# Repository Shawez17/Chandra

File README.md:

High Voltage Power Supply+ (remote operation)
=========================

```Markdown
1. When encoder rotates or value form the pc (out of 4086) is entered
# provides V out values on the display
# provide I out values on the display aswell, same goes for V in
2. When machine[esp32 and mains both] turned on.
# Led indicator glows
# startup provides 16 Volts and tranformer 18V to Pwm controller

```
MIT LICENSE
-----------

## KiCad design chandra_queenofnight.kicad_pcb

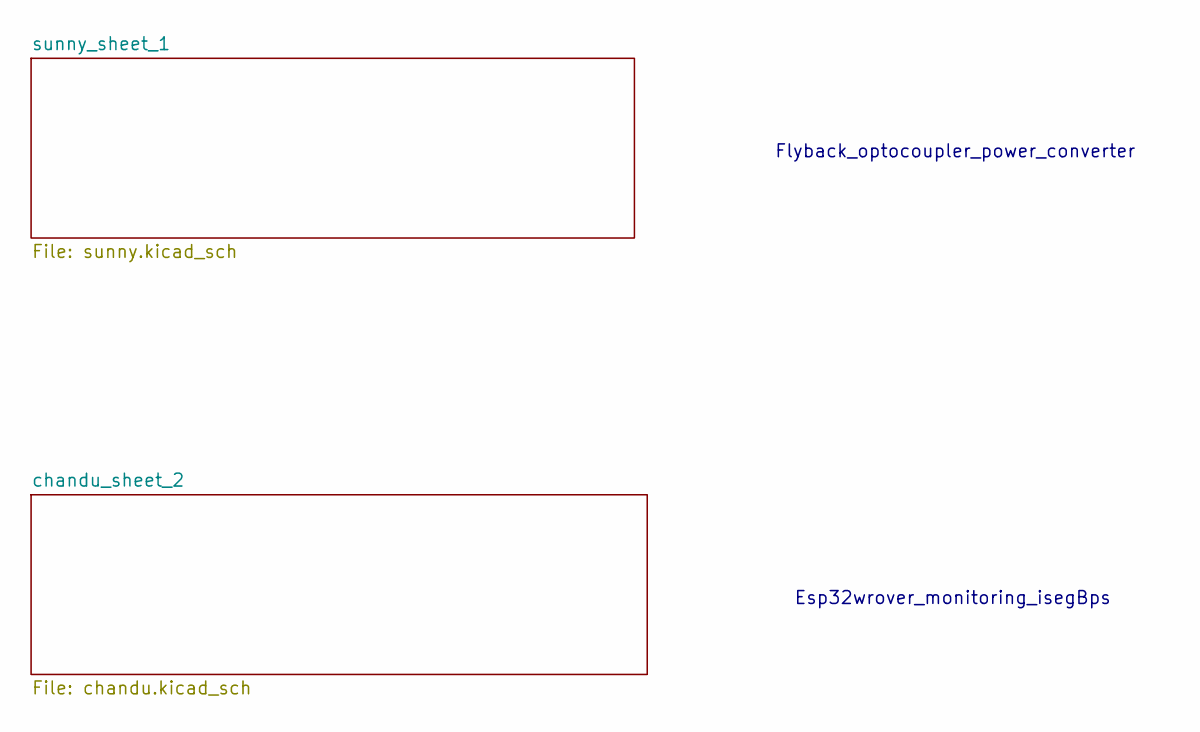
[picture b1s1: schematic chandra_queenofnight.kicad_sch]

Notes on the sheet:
Flyback_optocoupler_power_converter
Esp32wrover_monitoring_isegBps

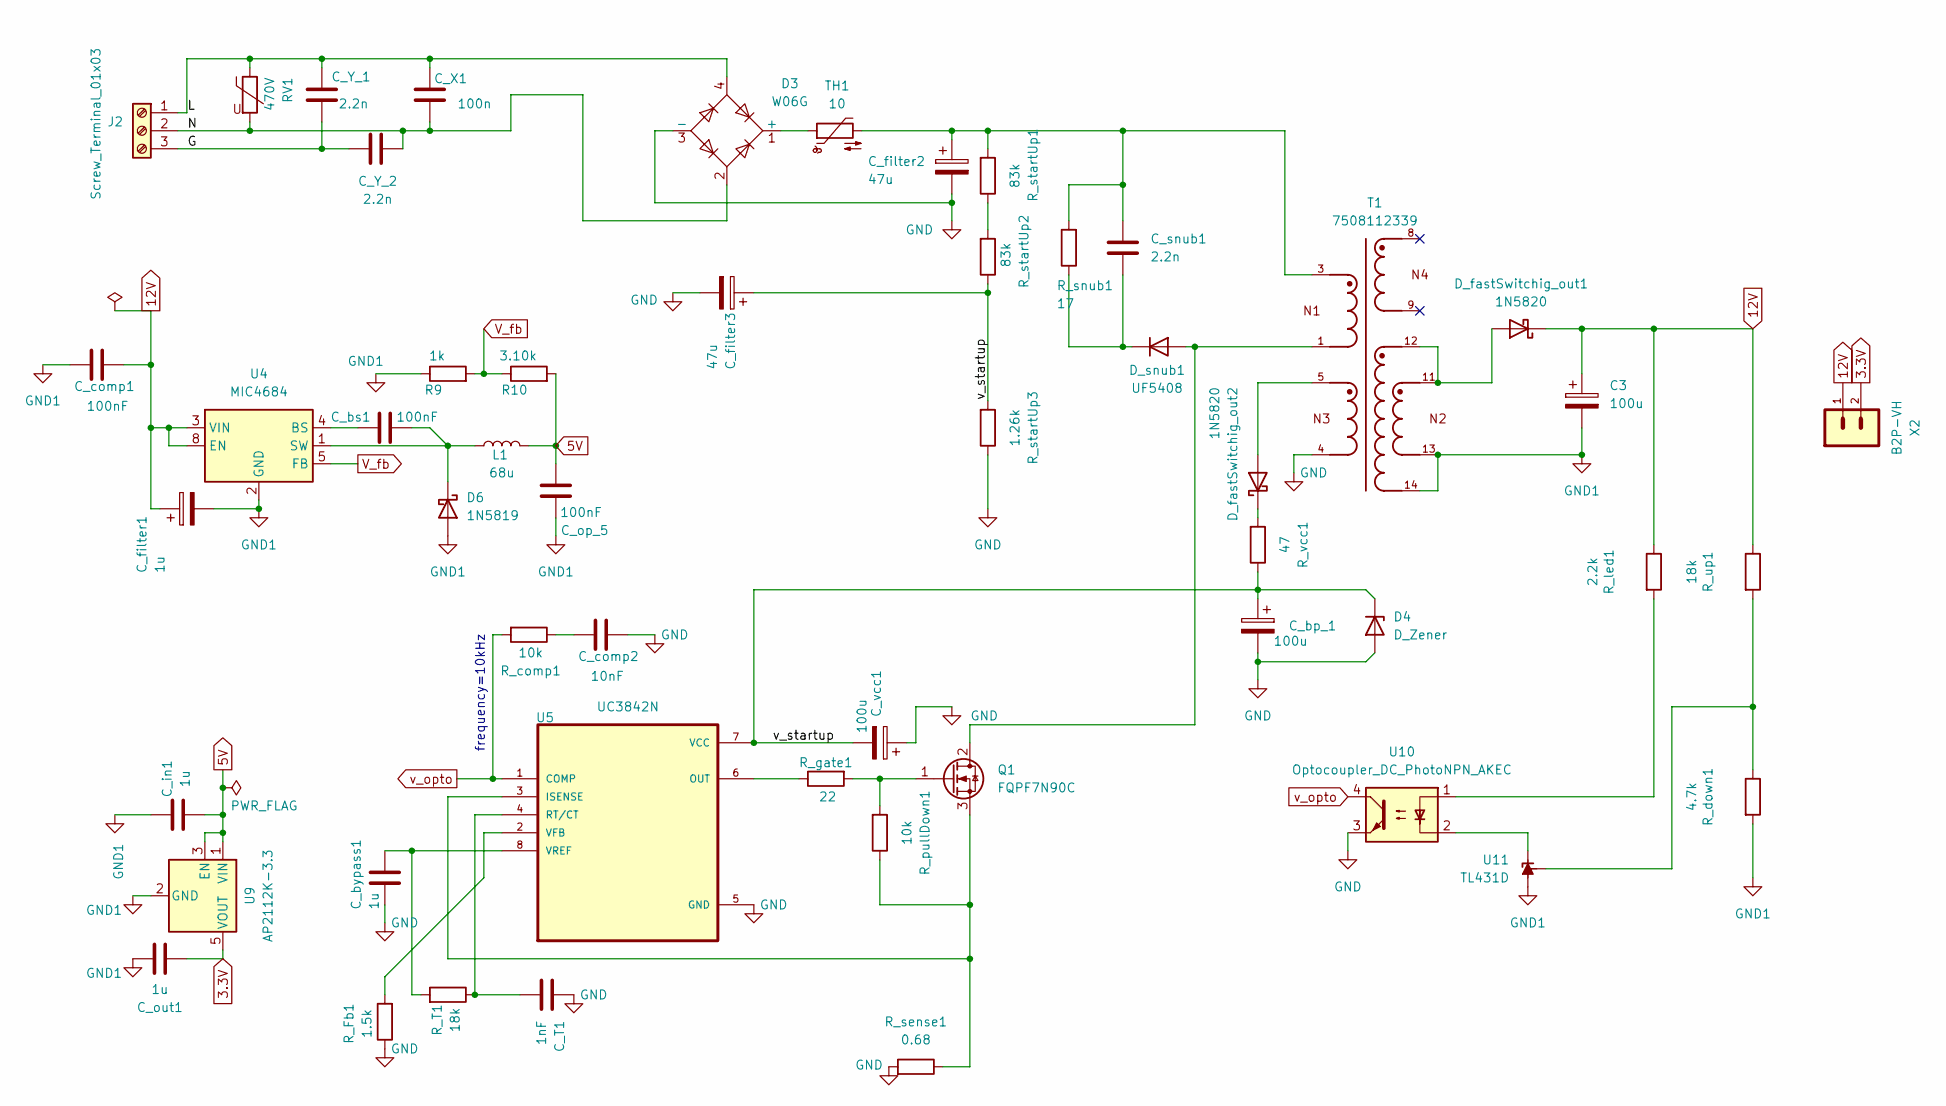
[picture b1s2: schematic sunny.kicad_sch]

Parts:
C3: 100u; CP_Radial_D10.0mm_P7.50mm
C_T1: 1nF; C_Disc_D5.0mm_W2.5mm_P5.00mm
C_X1: 100n; C_Rect_L10.0mm_W4.0mm_P7.50mm_MKS4
C_Y_1, C_Y_2: 2.2n; C_Rect_L7.2mm_W2.5mm_P5.00mm_FKS2_FKP2_MKS2_MKP2
C_bp_1: 100u; CP_Radial_D8.0mm_P3.50mm
C_bs1: 100nF; C_Disc_D5.0mm_W2.5mm_P5.00mm
C_bypass1: 1u; C_Disc_D5.0mm_W2.5mm_P5.00mm
C_comp1: 100nF; C_Disc_D5.0mm_W2.5mm_P5.00mm
C_comp2: 10nF; C_Disc_D10.5mm_W5.0mm_P10.00mm
C_filter1: 1u; CP_Radial_D5.0mm_P2.50mm
C_filter2, C_filter3: 47u; CP_Radial_D10.0mm_P7.50mm
C_in1: 1u; C_Disc_D10.0mm_W2.5mm_P5.00mm
C_op_5: 100nF; C_Disc_D5.0mm_W2.5mm_P5.00mm
C_out1: 1u; C_Disc_D10.0mm_W2.5mm_P5.00mm
C_snub1: 2.2n; C_Rect_L7.2mm_W2.5mm_P5.00mm_FKS2_FKP2_MKS2_MKP2
C_vcc1: 100u; CP_Radial_D10.0mm_P7.50mm
D3: W06G; Diode_Bridge_Round_D9.8mm
D4: D_Zener; D_5KP_P12.70mm_Horizontal
D6: 1N5819; D_DO-41_SOD81_P10.16mm_Horizontal
D_fastSwitchig_out1, D_fastSwitchig_out2: 1N5820; D_DO-15_P10.16mm_Horizontal
D_snub1: UF5408; D_DO-201AD_P15.24mm_Horizontal
J2: Screw_Terminal_01x03; TerminalBlock_MetzConnect_Type011_RT05503HBLC_1x03_P5.00mm_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
L1: 68u; L_Axial_L11.0mm_D4.5mm_P15.24mm_Horizontal_Fastron_MECC
Q1: FQPF7N90C; TO-220-3_Vertical
R9: 1k; R_Axial_DIN0207_L6.3mm_D2.5mm_P7.62mm_Horizontal
R10: 3.10k; R_Axial_DIN0207_L6.3mm_D2.5mm_P7.62mm_Horizontal
RV1: 470V; RV_Disc_D15.5mm_W5mm_P7.5mm
R_Fb1: 1.5k; R_Axial_DIN0204_L3.6mm_D1.6mm_P5.08mm_Horizontal
R_T1: 18k; R_Axial_DIN0414_L11.9mm_D4.5mm_P7.62mm_Vertical
R_comp1: 10k; R_Axial_DIN0207_L6.3mm_D2.5mm_P15.24mm_Horizontal
R_down1: 4.7k; R_Axial_DIN0207_L6.3mm_D2.5mm_P10.16mm_Horizontal
R_gate1: 22; R_Axial_DIN0207_L6.3mm_D2.5mm_P7.62mm_Horizontal
R_led1: 2.2k; R_Axial_DIN0309_L9.0mm_D3.2mm_P12.70mm_Horizontal
R_pullDown1: 10k; R_Axial_DIN0414_L11.9mm_D4.5mm_P7.62mm_Vertical
R_sense1: 0.68; R_Axial_DIN0411_L9.9mm_D3.6mm_P12.70mm_Horizontal
R_snub1: 17; R_Axial_DIN0411_L9.9mm_D3.6mm_P25.40mm_Horizontal
R_startUp1, R_startUp2: 83k; R_Axial_DIN0309_L9.0mm_D3.2mm_P20.32mm_Horizontal
R_startUp3: 1.26k; R_Axial_DIN0309_L9.0mm_D3.2mm_P20.32mm_Horizontal
R_up1: 18k; R_Axial_DIN0207_L6.3mm_D2.5mm_P7.62mm_Horizontal
R_vcc1: 47; R_Axial_DIN0411_L9.9mm_D3.6mm_P12.70mm_Horizontal
T1: 7508112339; WE-OLTI_EE20_10_6_L22.2W26H16.5
TH1: 10; R_Axial_DIN0207_L6.3mm_D2.5mm_P5.08mm_Vertical
U4: MIC4684; SOIC-8_3.9x4.9mm_P1.27mm
U5: UC3842N; DIP794W45P254L959H508Q8
U9: AP2112K-3.3; SOT-23-5
U10: Optocoupler_DC_PhotoNPN_AKEC; DIP-4_W7.62mm
U11: TL431D; SOIC-8_3.9x4.9mm_P1.27mm
X2: B2P-VH; JST_VH_B2P-VH-B_1x02_P3.96mm_Vertical

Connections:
5V: C_in1.2, C_op_5.2, L1.2, R10.2, U9.1 (VIN), U9.3 (EN)
/sunny_sheet_1/G: C_Y_1.2, C_Y_2.1, J2.3
/sunny_sheet_1/L: C_X1.1, C_Y_1.1, D3.4, J2.1, RV1.1
/sunny_sheet_1/N: C_X1.2, C_Y_2.2, D3.2, J2.2, RV1.2
/sunny_sheet_1/v_startup: C_bp_1.1, C_filter3.1, C_vcc1.2, D4.1 (K), R_startUp2.1, R_startUp3.2, R_vcc1.1, U5.7 (VCC)
GND: C_T1.1, C_bp_1.2, C_bypass1.1, C_comp2.1, C_filter2.2, C_filter3.2, C_vcc1.1, D3.3 (-), D4.2 (A), R_Fb1.1, R_sense1.2, R_startUp3.1, T1.4, U5.5 (GND), U10.3
GND1: C3.2, C_comp1.2, C_filter1.2, C_in1.1, C_op_5.1, C_out1.2, D6.2 (A), R9.1, R_down1.2, T1.13, T1.14, U4.2 (GND), U4.6 (GND), U4.7 (GND), U9.2 (GND), U11.2 (A), U11.3 (A), U11.6 (A), U11.7 (A); also elsewhere on the board
unnamed: C_comp2.2, R_comp1.1
unnamed: C_filter2.1, C_snub1.1, R_snub1.2, R_startUp1.2, T1.3, TH1.2
unnamed: D3.1 (+), TH1.1
unnamed: C_bs1.2, D6.1 (K), L1.1, U4.1 (SW)
unnamed: D_fastSwitchig_out1.2 (A), T1.11, T1.12
unnamed: D_fastSwitchig_out2.2 (A), T1.5
unnamed: D_fastSwitchig_out2.1 (K), R_vcc1.2
unnamed: D_snub1.2 (A), Q1.2 (D), T1.1
unnamed: C_snub1.2, D_snub1.1 (K), R_snub1.1
unnamed: Q1.1 (G), R_gate1.2, R_pullDown1.2
unnamed: Q1.3 (S), R_pullDown1.1, R_sense1.1, U5.3 (ISENSE)
unnamed: R_led1.2, U10.1
unnamed: R_startUp1.1, R_startUp2.2
unnamed: C_bs1.1, U4.4 (BS)
unnamed: R_gate1.1, U5.6 (OUT)
unnamed: C_T1.2, R_T1.1, U5.4 (RT/CT)
unnamed: R_Fb1.2, U5.2 (VFB)
unnamed: C_bypass1.2, R_T1.2, U5.8 (VREF)
unnamed: U10.2, U11.1 (K)
unnamed: R_down1.1, R_up1.2, U11.8 (REF)
V_fb: R9.2, R10.1, U4.5 (FB)
v_opto: R_comp1.2, U5.1 (COMP), U10.4

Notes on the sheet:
frequency=10kHz

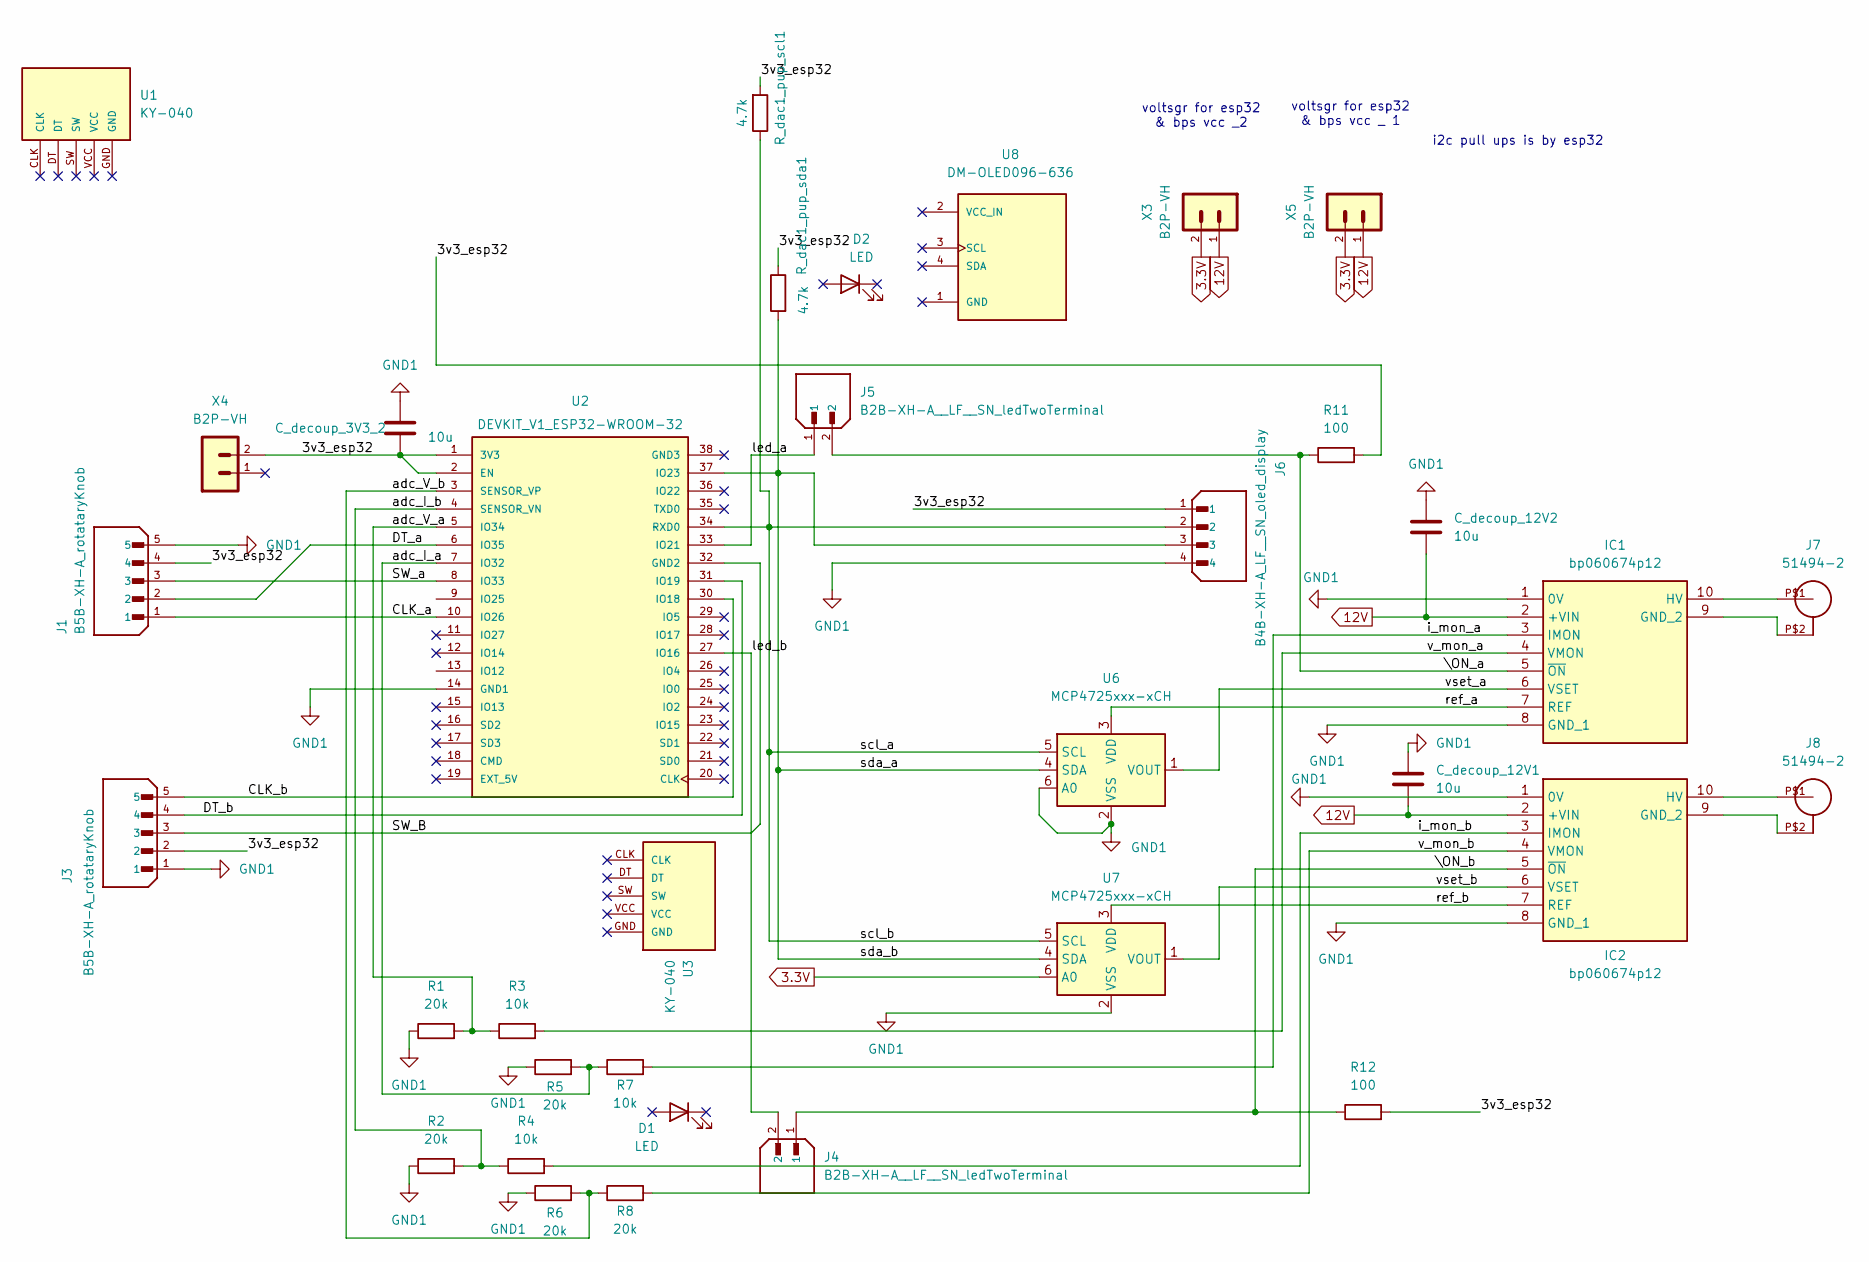
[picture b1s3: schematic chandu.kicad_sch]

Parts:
C_decoup_3V3_2, C_decoup_12V1, C_decoup_12V2: 10u; CP_Radial_D5.0mm_P2.00mm
D1, D2: LED; LED_D1.8mm_W1.8mm_H2.4mm_Horizontal_O3.81mm_Z4.9mm
IC1, IC2: bp060674p12; Manufacturer_Part_Number bp060674p12
J1, J3: B5B-XH-A_rotataryKnob; JST_B5B-XH-A; PARTREV 7/4/21
J4, J5: B2B-XH-A__LF__SN_ledTwoTerminal; JST_B2B-XH-A__LF__SN_; PARTREV N/A
J6: B4B-XH-A_LF__SN_oled_display; JST_B4B-XH-A_LF__SN_; PARTREV 7/4/21
J7, J8: 51494-2; DigiKey_Part_Number A24669-ND
R1, R2, R5, R6, R8: 20k; R_Axial_DIN0207_L6.3mm_D2.5mm_P7.62mm_Horizontal
R3, R4, R7: 10k; R_Axial_DIN0207_L6.3mm_D2.5mm_P7.62mm_Horizontal
R11, R12: 100; R_Axial_DIN0207_L6.3mm_D2.5mm_P2.54mm_Vertical
R_dac1_pup_scl1, R_dac1_pup_sda1: 4.7k; R_Axial_DIN0207_L6.3mm_D2.5mm_P7.62mm_Horizontal
U1, U3: KY-040; KY-040-PORT
U2: DEVKIT_V1_ESP32-WROOM-32; MODULE_DEVKIT_V1_ESP32-WROOM-32; PARTREV N/A
U6, U7: MCP4725xxx-xCH; SOT-23-6_Handsoldering
U8: DM-OLED096-636; MODULE_DM-OLED096-636; PARTREV 2018-09-10
X3, X4, X5: B2P-VH; JST_VH_B2P-VH-B_1x02_P3.96mm_Vertical

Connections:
/chandu_sheet_2/3v3_esp32: C_decoup_3V3_2.2, J1.4, J3.2, J6.1, R11.2, R12.2, R_dac1_pup_scl1.2, R_dac1_pup_sda1.1, U2.1 (3V3), U2.2 (EN), X4.2
/chandu_sheet_2/CLK_a: J1.1, U2.10 (IO26)
/chandu_sheet_2/CLK_b: J3.5, U2.30 (IO18)
/chandu_sheet_2/DT_a: J1.2, U2.6 (IO35)
/chandu_sheet_2/DT_b: J3.4, U2.31 (IO19)
/chandu_sheet_2/SW_B: J3.3, U2.32 (GND2)
/chandu_sheet_2/SW_a: J1.3, U2.8 (IO33)
/chandu_sheet_2/\ON_a: IC1.5 (~ON), J5.2, R11.1
/chandu_sheet_2/\ON_b: IC2.5 (~ON), J4.1, R12.1
/chandu_sheet_2/adc_I_a: R5.2, R7.1, U2.7 (IO32)
/chandu_sheet_2/adc_I_b: R2.2, R4.1, U2.4 (SENSOR_VN)
/chandu_sheet_2/adc_V_a: R1.2, R3.1, U2.5 (IO34)
/chandu_sheet_2/adc_V_b: R6.2, R8.1, U2.3 (SENSOR_VP)
/chandu_sheet_2/i_mon_a: IC1.3 (IMON), R7.2
/chandu_sheet_2/i_mon_b: IC2.3 (IMON), R4.2
/chandu_sheet_2/led_a: J5.1, U2.33 (IO21)
/chandu_sheet_2/led_b: J4.2, U2.27 (IO16)
/chandu_sheet_2/ref_a: IC1.7 (REF), U6.3 (VDD)
/chandu_sheet_2/ref_b: IC2.7 (REF), U7.3 (VDD)
/chandu_sheet_2/scl_a: J6.2, R_dac1_pup_scl1.1, U2.34 (RXD0), U6.5 (SCL), U7.5 (SCL)
/chandu_sheet_2/sda_a: J6.3, R_dac1_pup_sda1.2, U2.37 (IO23), U6.4 (SDA), U7.4 (SDA)
/chandu_sheet_2/v_mon_a: IC1.4 (VMON), R3.2
/chandu_sheet_2/v_mon_b: IC2.4 (VMON), R8.2
/chandu_sheet_2/vset_a: IC1.6 (VSET), U6.1 (VOUT)
/chandu_sheet_2/vset_b: IC2.6 (VSET), U7.1 (VOUT)
GND1: C_decoup_3V3_2.1, C_decoup_12V1.1, C_decoup_12V2.1, IC1.1 (0V), IC1.8 (GND_1), IC2.1 (0V), IC2.8 (GND_1), J1.5, J3.1, J6.4, R1.1, R2.1, R5.1, R6.1, U2.14 (GND1), U6.2 (VSS), U6.6 (A0), U7.2 (VSS); also elsewhere on the board
unnamed: IC1.9 (GND_2), J7.P$2
unnamed: IC1.10 (HV), J7.P$1
unnamed: IC2.9 (GND_2), J8.P$2
unnamed: IC2.10 (HV), J8.P$1

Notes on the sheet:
i2c pull ups is by esp32
voltsgr for esp32 & bps vcc _2
voltsgr for esp32 & bps vcc _ 1

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
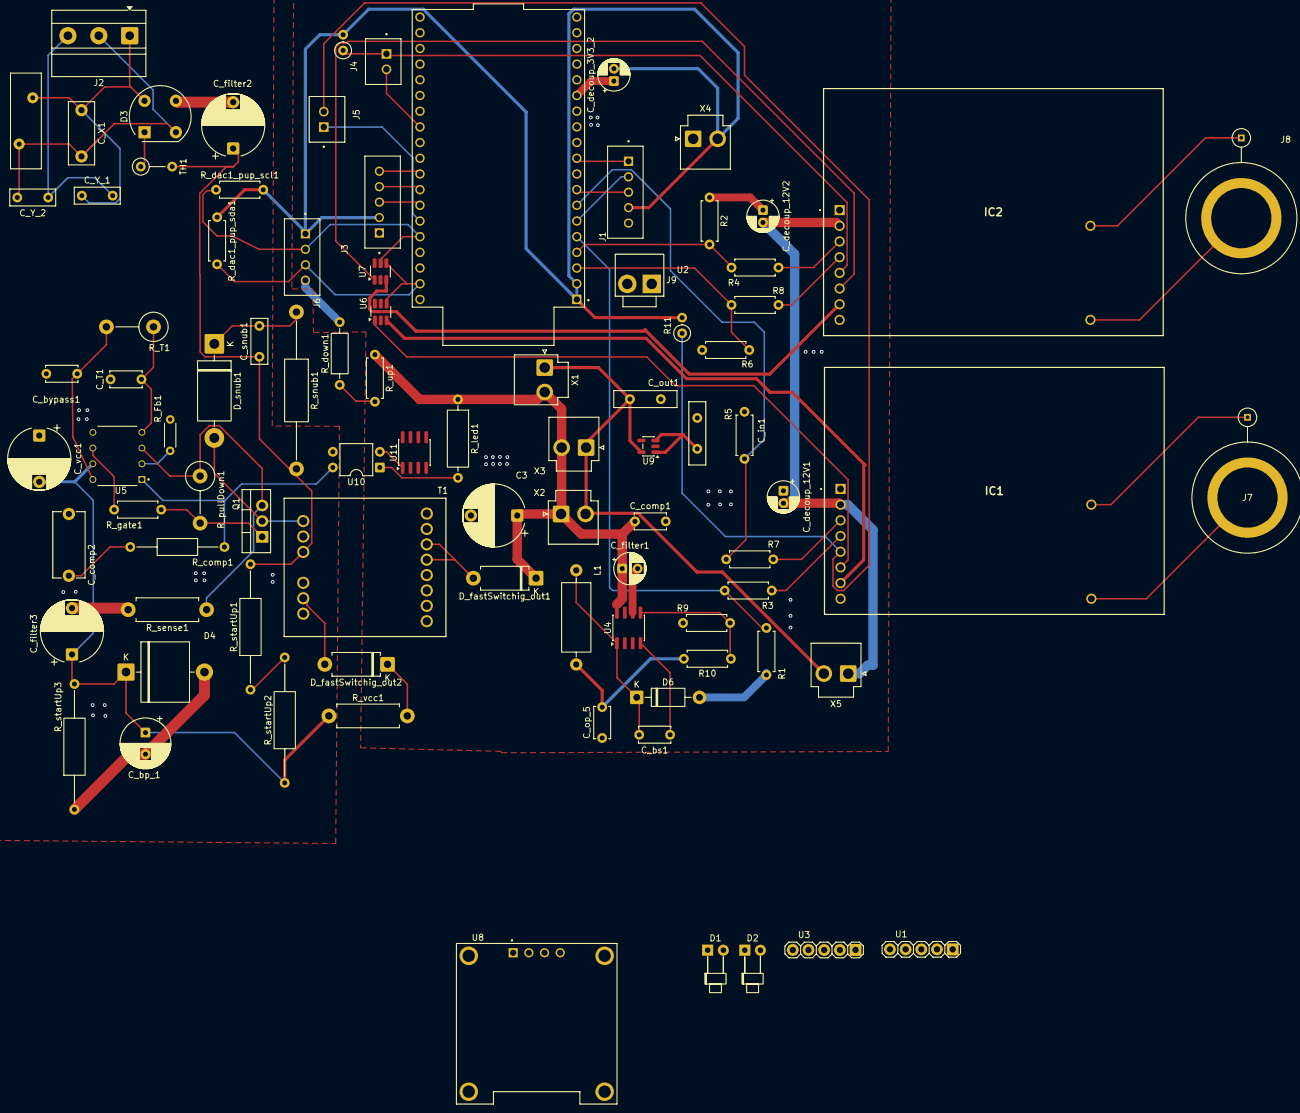
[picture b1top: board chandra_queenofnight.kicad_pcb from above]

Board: 2 copper layers, 89 parts (0 on the bottom side), 60 nets.

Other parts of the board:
J9: B2B-XH-A; B2P-VH
X1: B2P-VH; JST_VH_B2P-VH-B_1x02_P3.96mm_Vertical

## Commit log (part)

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2026-04-08 initialise global photo directory
2026-04-10 Initialtes
2026-04-10 Initialtes 1
2026-04-13 Initialtes 130426
2026-04-17 Initialtes gndplane
2026-04-21 Initialtes apr21
2026-04-22 Initialtes apr22
2026-04-24 Initialtes apr24
2026-04-25 Initialtes apr26
2026-04-28 Initialtes draft1
